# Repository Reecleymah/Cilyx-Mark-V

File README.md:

# Cilyx MK-V
## Proyecto: Generador de Señales de Reloj y PWM con NE555

Este proyecto consiste en la implementación de un generador de señales de reloj y PWM utilizando el temporizador **NE555**. El circuito permite cambiar entre diferentes rangos de frecuencia y ajustar la frecuencia de salida mediante un potenciómetro. Esto lo hace ideal para la enseñanza y práctica de temas relacionados con sistemas digitales, donde las señales de reloj y PWM son esenciales.

## Objetivo del Proyecto
Desarrollar una tarjeta PCB que sirva como una herramienta educativa para estudiantes de sistemas digitales. La tarjeta permitirá generar señales de reloj ajustables y experimentar con distintos rangos de frecuencia. Además, se proporciona una visualización de la señal a través de LEDs, lo que ayuda a entender la relación entre frecuencia y tiempo de encendido/apagado.

## Listado de Componentes

| Componente        | Valor               | Cantidad | Descripción                                                                 |
|-------------------|---------------------|----------|-----------------------------------------------------------------------------|
| NE555             | -                   | 1        | Temporizador configurado en modo astable para generar la señal de salida.   |
| Resistencia       | 1kΩ                 | 1        | Limita la corriente al LED de encendido.                                    |
| Resistencia       | 330Ω                | 1        | Limita la corriente al LED de señal.                                        |
| Resistencia       | 2.7kΩ               | 1        | Parte del ajuste de la frecuencia del NE555.                                |
| Resistencia       | 47kΩ                | 1        | Parte del ajuste de la frecuencia del NE555.                                |
| Potenciómetro     | 500kΩ               | 1        | Permite ajustar la frecuencia de salida dentro del rango seleccionado.      |
| Condensador       | 100 nF, 10 nF, 1 nF | 1 c/u    | Define el rango de frecuencia junto al interruptor.                         |
| Condensador       | 10 nF               | 1        | Filtra la señal de alimentación del NE555.                                  |
| LED               | -                   | 2        | Uno para indicar encendido y otro para visualizar la señal de salida.       |
| Interruptor       | 1P3T (3 posiciones) | 1        | Cambia entre los rangos de frecuencia usando diferentes condensadores.      |
| Fuente de Alimentación | 5V            | 1        | Suministra voltaje al circuito.                                             |

## Funcionamiento del Circuito

1. **Configuración Astable del NE555**:
   - El temporizador NE555 está configurado en modo astable para generar una señal de onda cuadrada continua en su pin de salida (pin 3).
   - La frecuencia de la señal de salida se determina mediante los valores de las resistencias y los condensadores conectados al NE555.
   - Los valores de las resistencias y el condensador principal en la configuración astable afectan directamente la frecuencia y el duty cycle de la señal.

2. **Selección de Rango de Frecuencia**:
   - El interruptor de 3 posiciones permite cambiar entre tres condensadores de diferentes valores (100 nF, 10 nF y 1 nF), lo cual ajusta el rango de frecuencia de la señal:
     - **100 nF (Posición A)**: Rango de frecuencia de 10 Hz a ~130 Hz.
     - **10 nF (Posición B)**: Rango de frecuencia de 130 Hz a ~1 kHz.
     - **1 nF (Posición C)**: Rango de frecuencia de 1 kHz a ~10 kHz.
   - El usuario puede seleccionar el rango deseado para su experimento.

3. **Ajuste Fino de Frecuencia**:
   - Un potenciómetro de 500kΩ permite ajustar la frecuencia de salida dentro del rango seleccionado, proporcionando una señal de reloj de frecuencia variable.
   - Este ajuste fino es ideal para observar el efecto de diferentes frecuencias en sistemas digitales, como contadores o flip-flops.

4. **Visualización de la Señal**:
   - Un LED de señal (con una resistencia limitadora de 330Ω) está conectado a la salida del NE555 y parpadea según la frecuencia generada. Esto permite una visualización rápida de la señal sin necesidad de un osciloscopio.
   - Además, se incluye un LED de encendido (con una resistencia de 1kΩ) para indicar que el circuito está en funcionamiento.

## Funcionamiento Previsto
El circuito generará una señal de reloj con frecuencia ajustable, útil para sistemas digitales. Cambiando la posición del interruptor, el usuario puede seleccionar el rango de frecuencia deseado. El potenciómetro permite hacer ajustes finos dentro de ese rango, y el LED de señal permite una verificación visual de la salida. Este diseño facilita la comprensión de conceptos de frecuencia y duty cycle, así como la relación entre frecuencia y temporización en circuitos digitales.

El circuito puede emplearse para:
- **Sincronización de Circuitos Digitales**: Proveer una señal de reloj a contadores, flip-flops o microcontroladores.
- **Generación de PWM Básico**: Con pequeños ajustes en los valores de resistencia, también puede utilizarse para generar una señal de PWM simple.
- **Aprendizaje Práctico**: Ideal para estudiantes de electrónica y sistemas digitales para experimentar con señales de temporización.

---

Este proyecto proporciona una base sólida para la enseñanza de conceptos de temporización y señales en sistemas digitales. Además, es una herramienta útil en un laboratorio de electrónica donde los estudiantes pueden explorar de manera práctica los principios de la frecuencia y el duty cycle.

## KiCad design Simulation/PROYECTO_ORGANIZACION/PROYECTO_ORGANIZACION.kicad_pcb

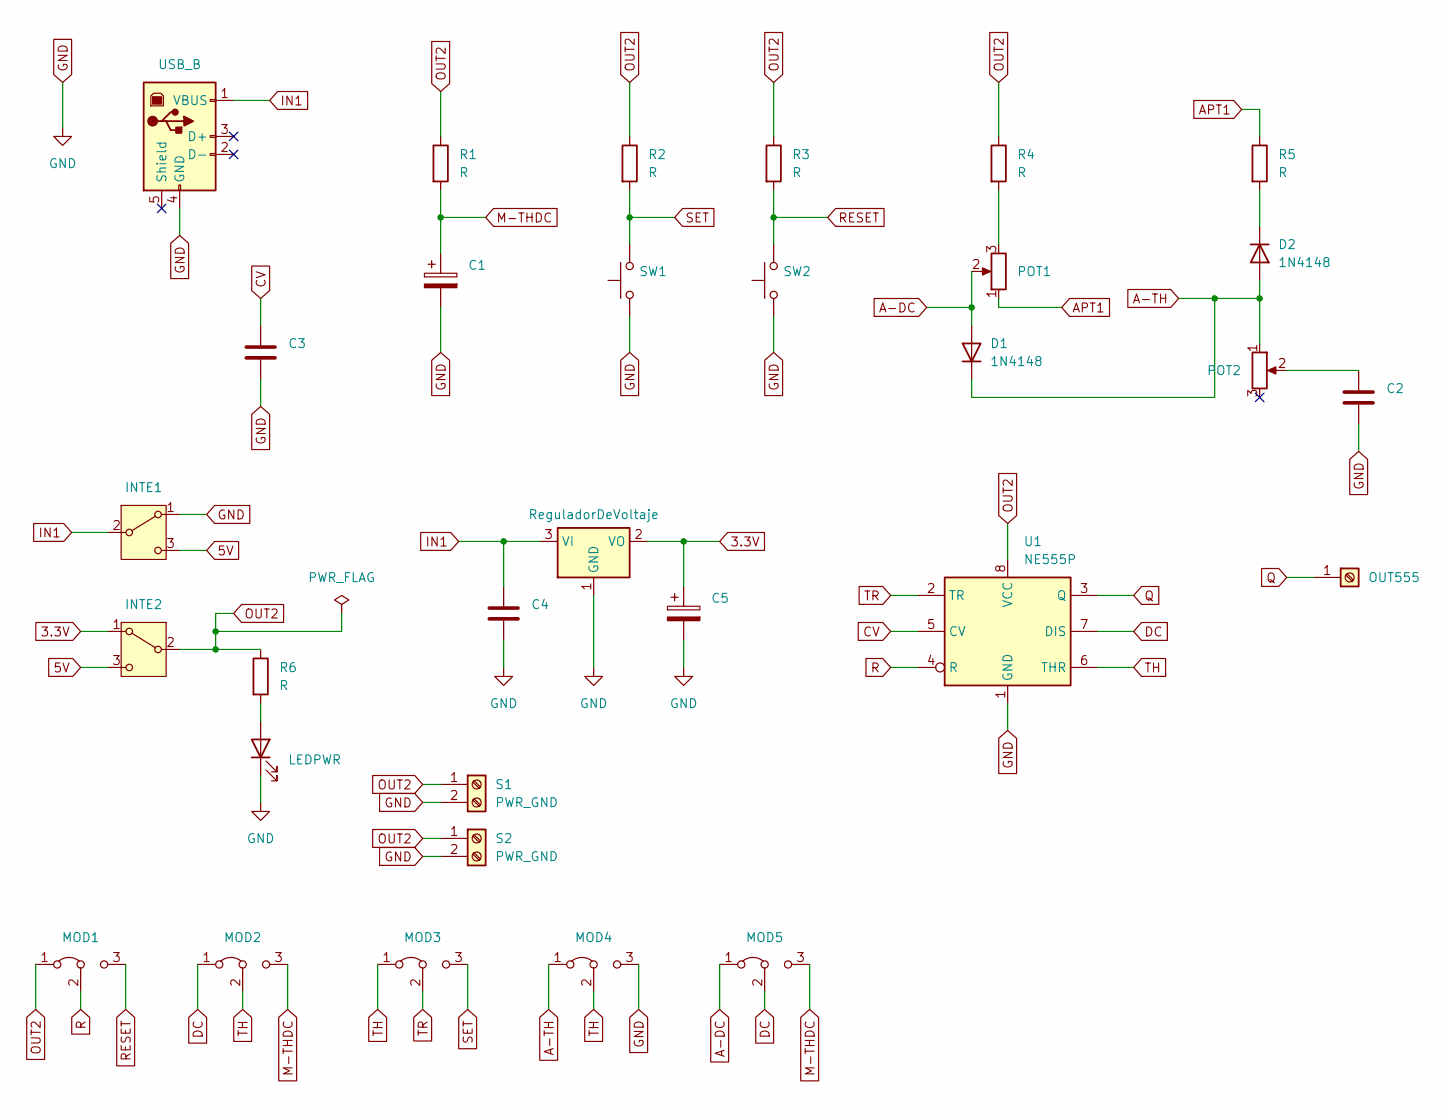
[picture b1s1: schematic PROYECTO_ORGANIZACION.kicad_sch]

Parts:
C1: C_Polarized; CP_Radial_D6.3mm_P2.50mm
C2, C4: C; CP_Radial_D8.0mm_P2.50mm
C3: C; C_Disc_D7.5mm_W5.0mm_P7.50mm
C5: C_Polarized; CP_Radial_D8.0mm_P3.50mm
D1, D2: 1N4148; D_DO-35_SOD27_P7.62mm_Horizontal
D3: LEDPWR; LED_D3.0mm
J1: USB_B; USB_B_Lumberg_2411_02_Horizontal
J4: OUT555; TerminalBlock_bornier-2_P5.08mm
JP1: MOD1; TerminalBlock_bornier-3_P5.08mm
JP2: MOD2; TerminalBlock_bornier-3_P5.08mm
JP3: MOD3; TerminalBlock_bornier-3_P5.08mm
JP4: MOD4; TerminalBlock_bornier-3_P5.08mm
JP5: MOD5; TerminalBlock_bornier-3_P5.08mm
POT2: R_Potentiometer; TerminalBlock_bornier-3_P5.08mm
R1, R2, R3, R4, R5, R6: R; R_Axial_DIN0207_L6.3mm_D2.5mm_P7.62mm_Horizontal
RV1: POT1; TerminalBlock_bornier-3_P5.08mm
S1, S2: PWR_GND; TerminalBlock_bornier-2_P5.08mm
SW1, SW2: SW_Push; SW_PUSH_1P1T_6x3.5mm_H4.3_APEM_MJTP1243
SW3: INTE1; SW_Slide-03_Wuerth-WS-SLTV_10x2.5x6.4_P2.54mm
SW4: INTE2; SW_Slide-03_Wuerth-WS-SLTV_10x2.5x6.4_P2.54mm
U1: NE555P; DIP-8_W7.62mm
U2: ReguladorDeVoltaje; TO-220F-3_Vertical

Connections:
3.3V: C5.1, SW4.1 (A), U2.2 (VO)
5V: SW3.3 (C), SW4.3 (C)
A-DC: D1.2 (A), JP5.1 (A), RV1.2
A-TH: D1.1 (K), D2.2 (A), JP4.1 (A), POT2.1
APT1: R5.1, RV1.1
CV: C3.1, U1.5 (CV)
DC: JP2.1 (A), JP5.2 (C), U1.7 (DIS)
GND: C1.2, C2.2, C3.2, C4.2, C5.2, D3.1 (K), J1.4 (GND), JP4.3 (B), S1.2, S2.2, SW1.1, SW2.1, SW3.1 (A), U1.1 (GND), U2.1 (GND)
IN1: C4.1, J1.1 (VBUS), SW3.2 (B), U2.3 (VI)
M-THDC: C1.1, JP2.3 (B), JP5.3 (B), R1.2
unnamed: C2.1, POT2.2
unnamed: D2.1 (K), R5.2
unnamed: D3.2 (A), R6.2
unnamed: R4.2, RV1.3
OUT2: JP1.1 (A), R1.1, R2.1, R3.1, R4.1, R6.1, S1.1, S2.1, SW4.2 (B), U1.8 (VCC)
Q: J4.1, U1.3 (Q)
R: JP1.2 (C), U1.4 (R)
RESET: JP1.3 (B), R3.2, SW2.2
SET: JP3.3 (B), R2.2, SW1.2
TH: JP2.2 (C), JP3.1 (A), JP4.2 (C), U1.6 (THR)
TR: JP3.2 (C), U1.2 (TR)

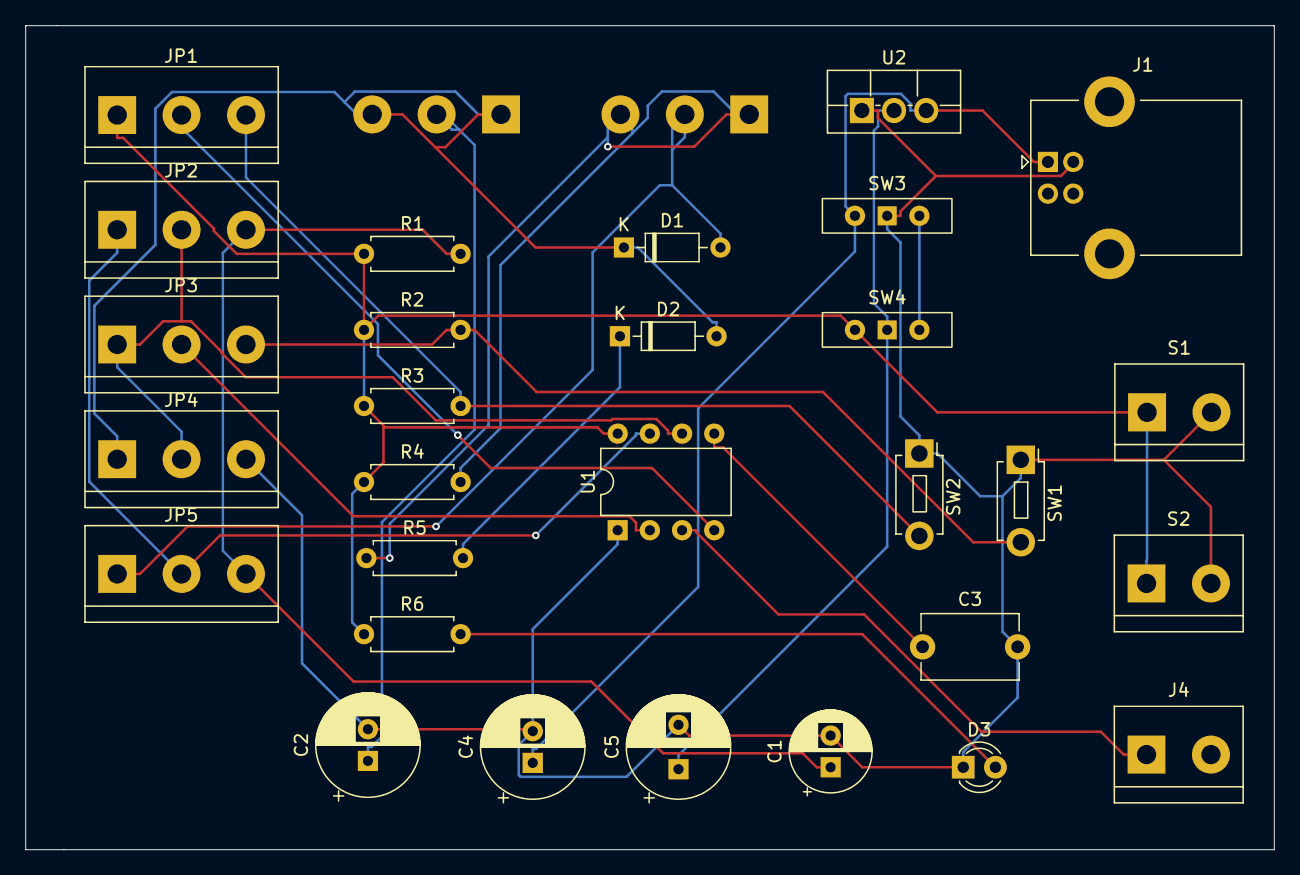
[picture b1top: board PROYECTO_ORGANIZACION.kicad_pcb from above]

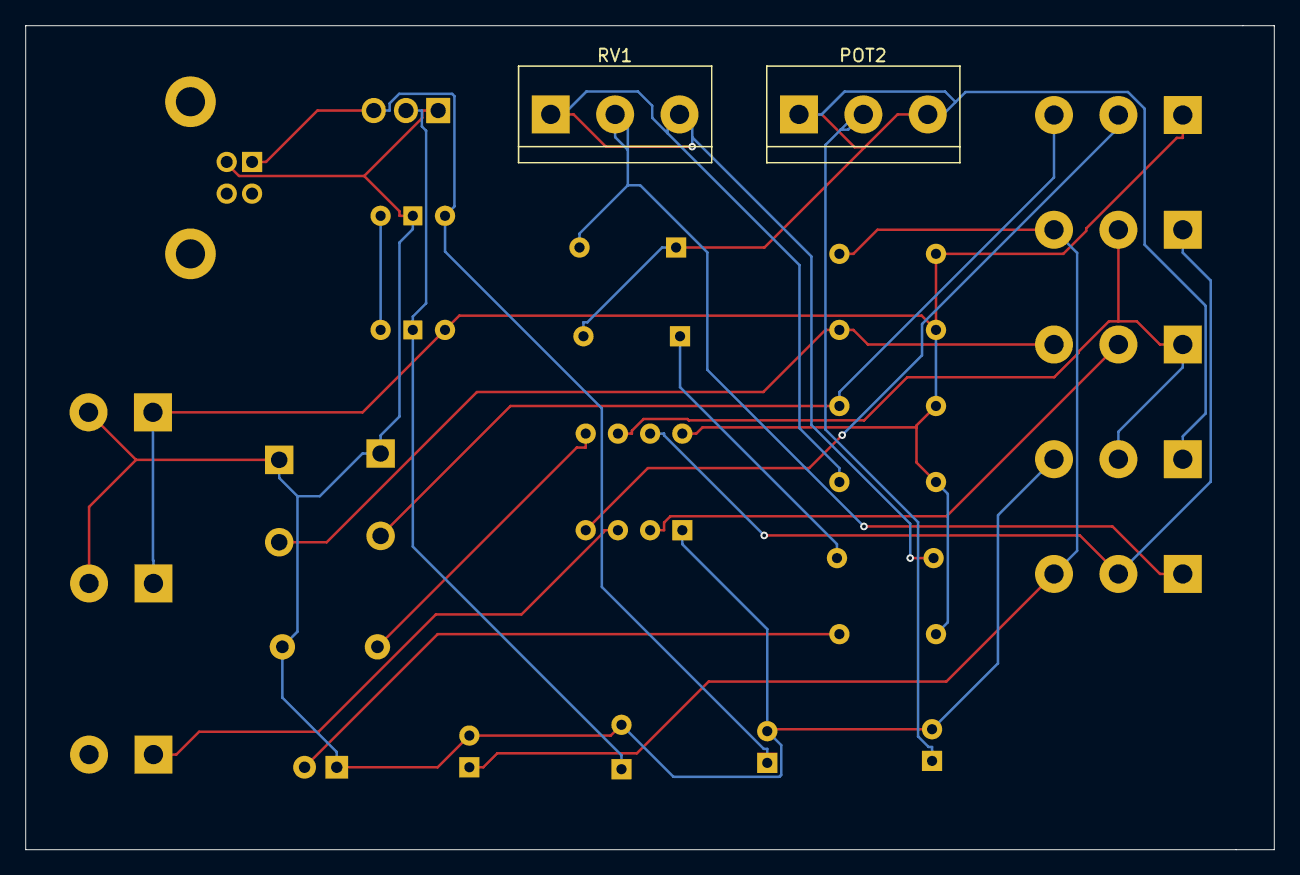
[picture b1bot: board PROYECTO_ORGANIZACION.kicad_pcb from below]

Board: 2 copper layers, 98.5 x 65.0 mm, 31 parts (2 on the bottom side), 21 nets.

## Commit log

2024-10-18 Create readmeS,md
2024-10-18 Create readmeR,md
2024-10-18 Create a
2024-10-18 AMS1117 Datasheets upload
2024-10-18 USB B Upload
2024-10-18 SS14 upload
2024-10-18 Bourns Datasheet upload
2024-10-27 Upload Simulation CylyxMKV
    Esta carga contiene:
    * Simulación en Proteus, de los modos (Biestable, Monoestable, Astable) del NE555, dichos modos están por separado, ósea son tres NE555.
2024-10-27 Upload Simulation Cilyx MkV
    Se agregó una sección de leds generales, para visualizar la frecuencia y funcionamiento de cada NE555
2024-11-01 Upload CilyxMkV
    Se integro de manera optimizada, los tres modos del NE555 (Monoestable, Biestable, y Astable). Usando solo un NE555
2024-11-01 Upload Schematic
2024-11-01 Vide Tutorial
2024-11-17 Diseño de PCB
    Esquemático y PCB
